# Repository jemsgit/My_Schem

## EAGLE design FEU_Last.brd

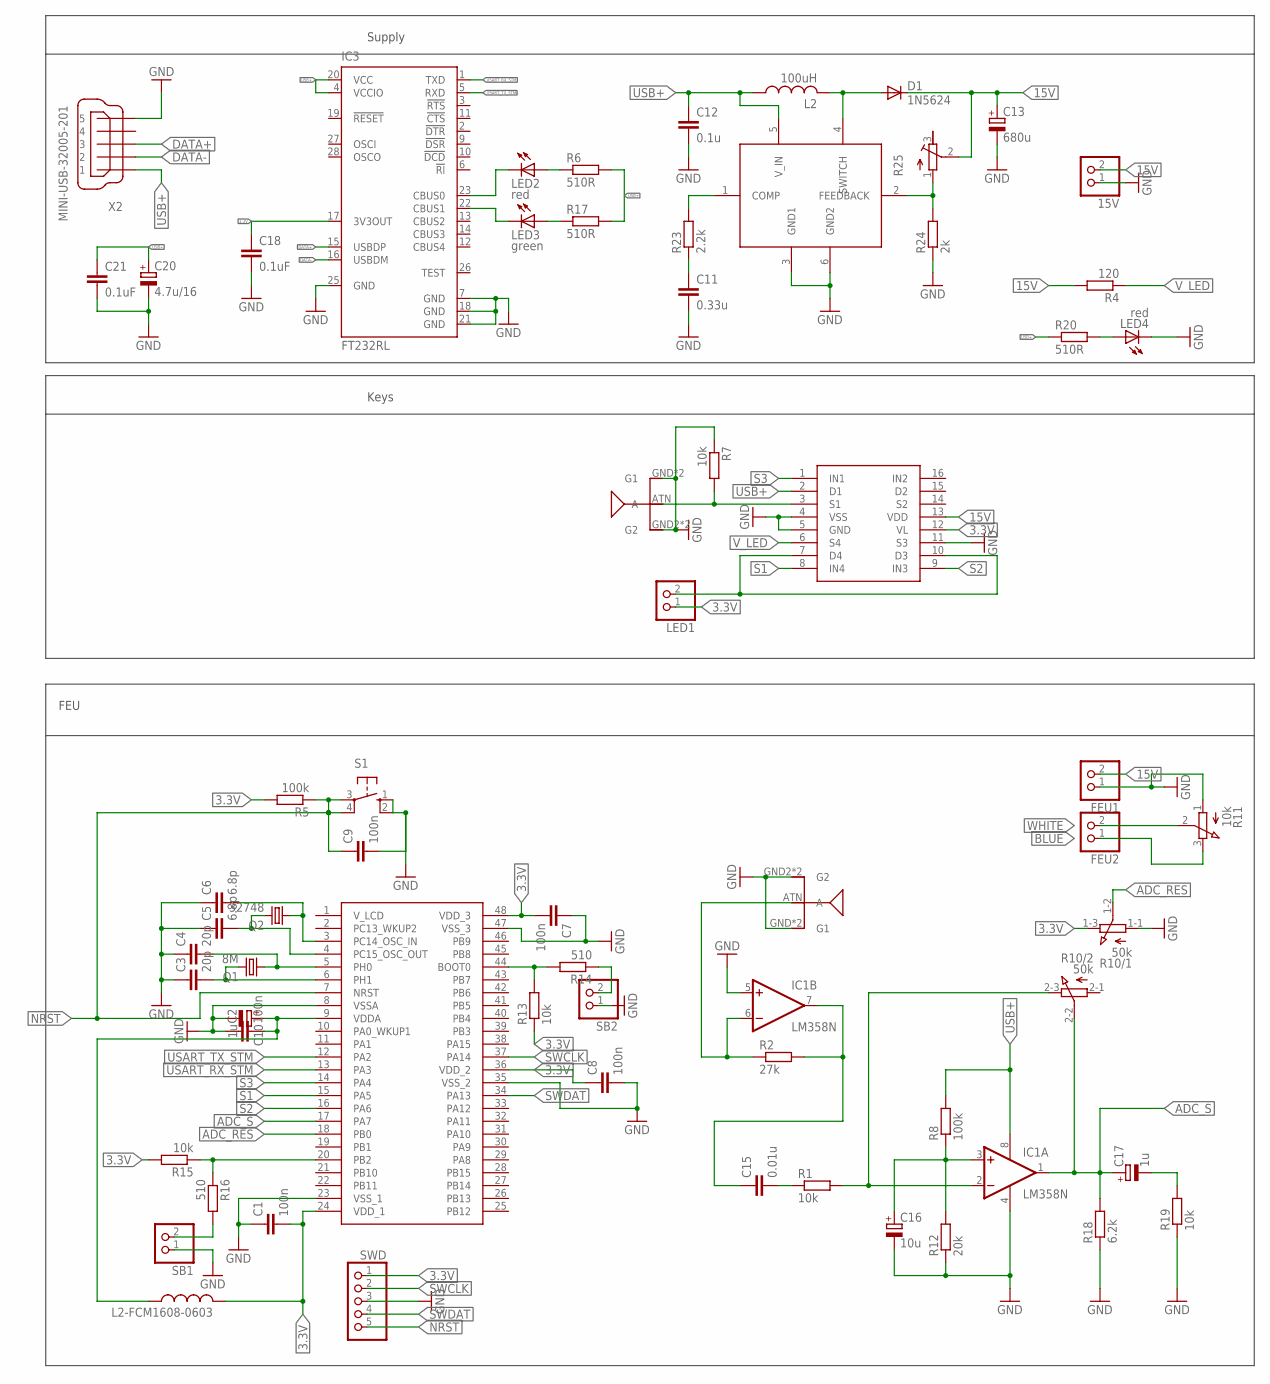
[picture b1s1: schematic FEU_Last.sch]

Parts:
15V: PINHD-1X2; 1X02
C1, C2, C7, C8, C9: 100n; C0805
C3, C4: 20p; C0805
C5, C6: 6.8p; C0805
C10: 1u; A/3216-18W
C11: 0.33u; C0805
C12: 0.1u; C0805
C13: 680u; E5-5
C15: 0.01u; C0805
C16: 10u; E3,5-8
C17: 1u; E3,5-8
C18, C21: 0.1uF; C0805
C20: 4.7u/16; E2-5
D1: 1N5624; DO201-15
FEU1, FEU2: PINHD-1X2; 1X02
IC1: LM358N; DIL08
IC3: FT232RL; SSOP28
L2: 100uH; 0207/5V
L2-FCM1608-0603: L-USL3216C; L3216C
LED1: PINHD-1X2; 1X02
LED2, LED4: red; CHIPLED_1206
LED3: green; CHIPLED_1206
Q1: 8M; HC49/S
Q2: 32748; TC26H
R1, R7, R13, R19: 10k; R0805
R2: 27k; R0805
R4: 120; R0805
R5, R8: 100k; R0805
R6, R17, R20: 510R; R0805W
R10: 50k; 3RP/1610G
R11: 10k; 3RP/1610N
R12: 20k; R0805
R14, R16: 510; R0805
R15: 10k; M0805
R18: 6.2k; R0805
R23: 2.2k; R0805
R24: 2k; R0805
R25: R-TRIMM3339P; RTRIM3339P
S1: 10-XX; B3F-10XX
SB1, SB2: PINHD-1X2; 1X02
SWD: PINHD-1X5; 1X05
U$1: STM32L152C6; LQFP48
U$2, U$3: GSM_ANT; GSM
U$4: LM2577; TO263-5
U$5: ADG433BN; DIL16
X2: MINI-USB-32005-201; 32005-201

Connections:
3.3V: C1.2, C7.2, C8.1, C18.1, IC3.17 (3V3OUT), L2-FCM1608-0603.2, LED1.1, R5.2, R10.1-3 (E), R13.1, R15.2, SWD.1, U$1.24 (VDD_1), U$1.36 (VDD_2), U$1.48 (VDD_3), U$5.12 (VL)
15V: 15V.2, C13.+, D1.C, FEU1.2, R4.2, R25.2 (S), U$5.13 (VDD)
ADC_RES: R10.1-2 (S), U$1.18 (PB0)
ADC_S: C17.+, IC1.1 (OUT), R10.2-2 (S), R18.2, U$1.17 (PA7)
BLUE: FEU2.1, R11.3 (E)
DATA+: IC3.15 (USBDP), X2.3
DATA-: IC3.16 (USBDM), X2.2
GND: 15V.1, C1.1, C2.1, C3.1, C4.1, C5.1, C6.1, C7.1, C8.2, C9.2, C10.-, C11.2, C12.2, C13.-, C16.-, C18.2, C20.-, C21.2, FEU1.1, IC1.4 (V-), IC1.5 (+IN), IC3.7 (GND), IC3.18 (GND), IC3.21 (GND), IC3.25 (GND), LED4.C, R7.1, R10.1-1 (A), R11.1 (A), R12.1, R18.1, R19.1, R24.1, S1.1 (S), S1.2 (S1), SB1.1, SB2.1, SWD.3, U$1.8 (VSSA), U$1.23 (VSS_1), U$1.35 (VSS_2), U$1.47 (VSS_3), U$2.GND (G1), U$2.GND1 (G1), U$2.GND2 (G2), U$2.GND3 (G2), U$3.GND (G1), U$3.GND1 (G1), U$3.GND2 (G2), U$3.GND3 (G2), U$4.3 (GND1), U$4.6 (GND2), U$5.4 (VSS), U$5.5 (GND), U$5.11 (S3), X2.5
unnamed: C4.2, Q1.1, U$1.5 (PH0)
unnamed: C3.2, Q1.2, U$1.6 (PH1)
unnamed: IC3.22 (CBUS1), LED3.C
unnamed: LED1.2, U$5.7 (D4), U$5.10 (D3)
unnamed: IC3.23 (CBUS0), LED2.C
unnamed: IC1.6 (-IN), R2.1, U$2.ATN (A)
unnamed: C15.1, IC1.7 (OUT), R2.2
unnamed: C15.2, R1.1
unnamed: C16.+, IC1.3 (+IN), R8.1, R12.2
unnamed: IC1.2 (-IN), R1.2, R10.2-3 (E)
unnamed: LED2.A, R6.1
unnamed: C5.2, Q2.2, U$1.4 (PC15_OSC_OUT)
unnamed: C6.2, Q2.1, U$1.3 (PC14_OSC_IN)
unnamed: C2.2, C10.+, L2-FCM1608-0603.1, U$1.9 (VDDA)
unnamed: R13.2, R14.2, U$1.44 (BOOT0)
unnamed: R16.2, SB1.2
unnamed: R14.1, SB2.2
unnamed: R15.1, R16.1, U$1.20 (PB2)
unnamed: C17.-, R19.2
unnamed: LED3.A, R17.1
unnamed: R7.2, U$3.ATN (A), U$5.3 (S1)
unnamed: LED4.A, R20.2
unnamed: R23.2, U$4.1 (COMP)
unnamed: C11.1, R23.1
unnamed: R24.2, R25.1 (E), U$4.2 (FEEDBACK)
unnamed: D1.A, L2.2, U$4.4 (SWITCH)
NRST: C9.1, R5.1, S1.3, S1.4 (P1), SWD.5, U$1.7 (NRST)
S1: U$1.15 (PA5), U$5.8 (IN4)
S2: U$1.16 (PA6), U$5.9 (IN3)
S3: U$1.14 (PA4), U$5.1 (IN1)
SWCLK: SWD.2, U$1.37 (PA14)
SWDAT: SWD.4, U$1.34 (PA13)
USART_RX_STM: IC3.1 (TXD), U$1.13 (PA3)
USART_TX_STM: IC3.5 (RXD), U$1.12 (PA2)
USB+: C12.1, C20.+, C21.1, IC1.8 (V+), IC3.4 (VCCIO), IC3.20 (VCC), L2.1, R6.2, R8.2, R17.2, R20.1, U$4.5 (V_IN), U$5.2 (D1), X2.1
V_LED: R4.1, U$5.6 (S4)
WHITE: FEU2.2, R11.2 (S)

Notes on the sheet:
Supply
Keys
FEU

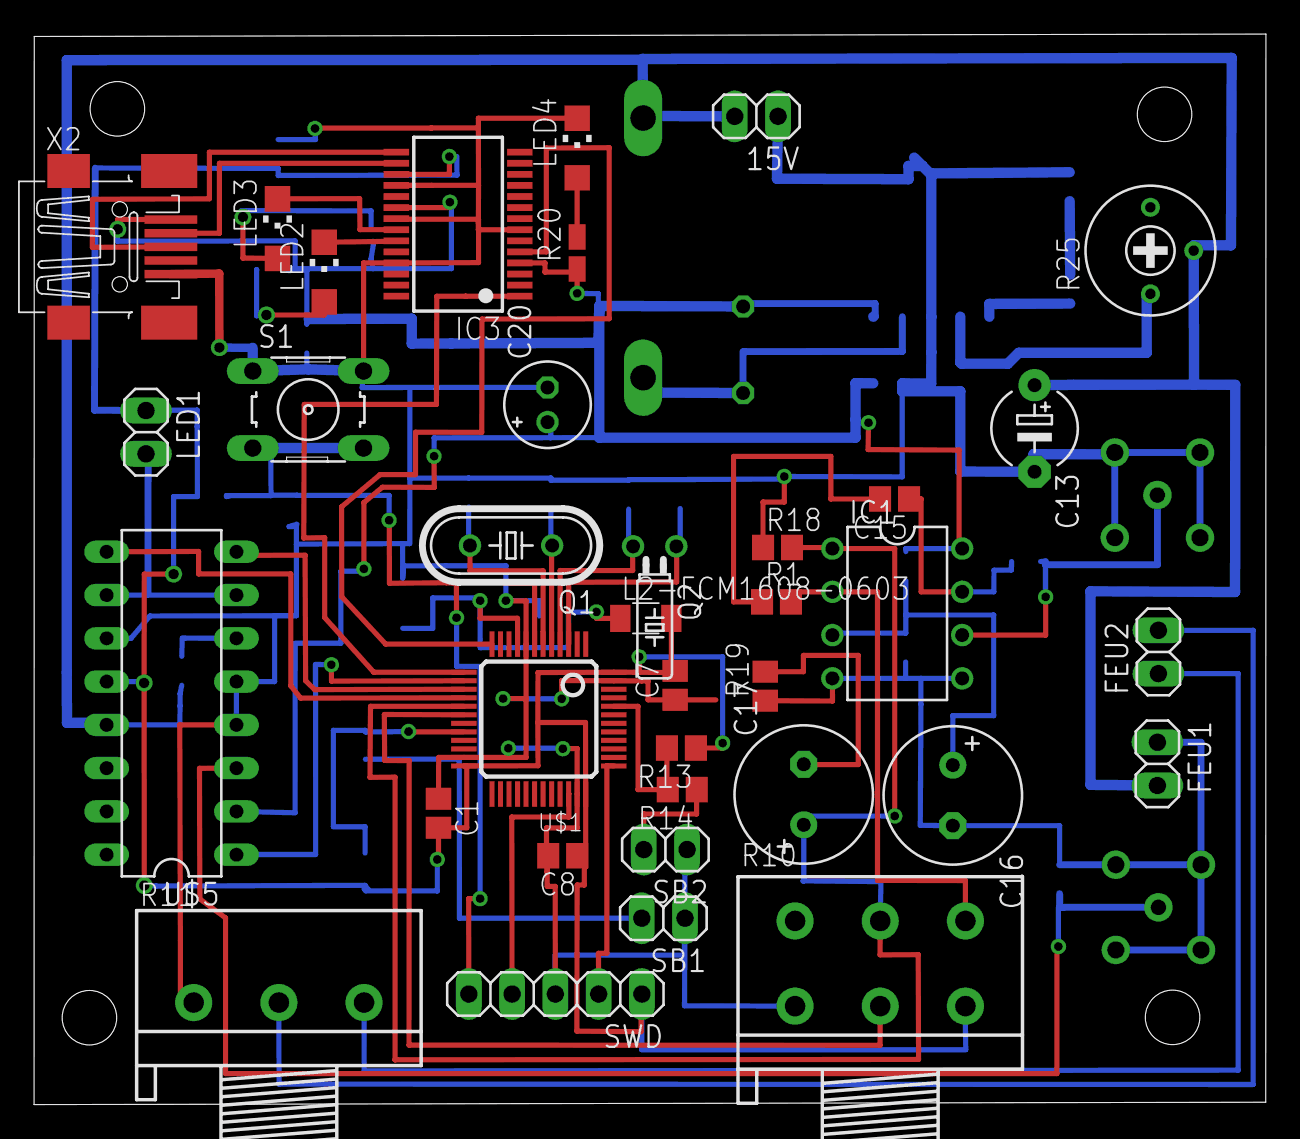
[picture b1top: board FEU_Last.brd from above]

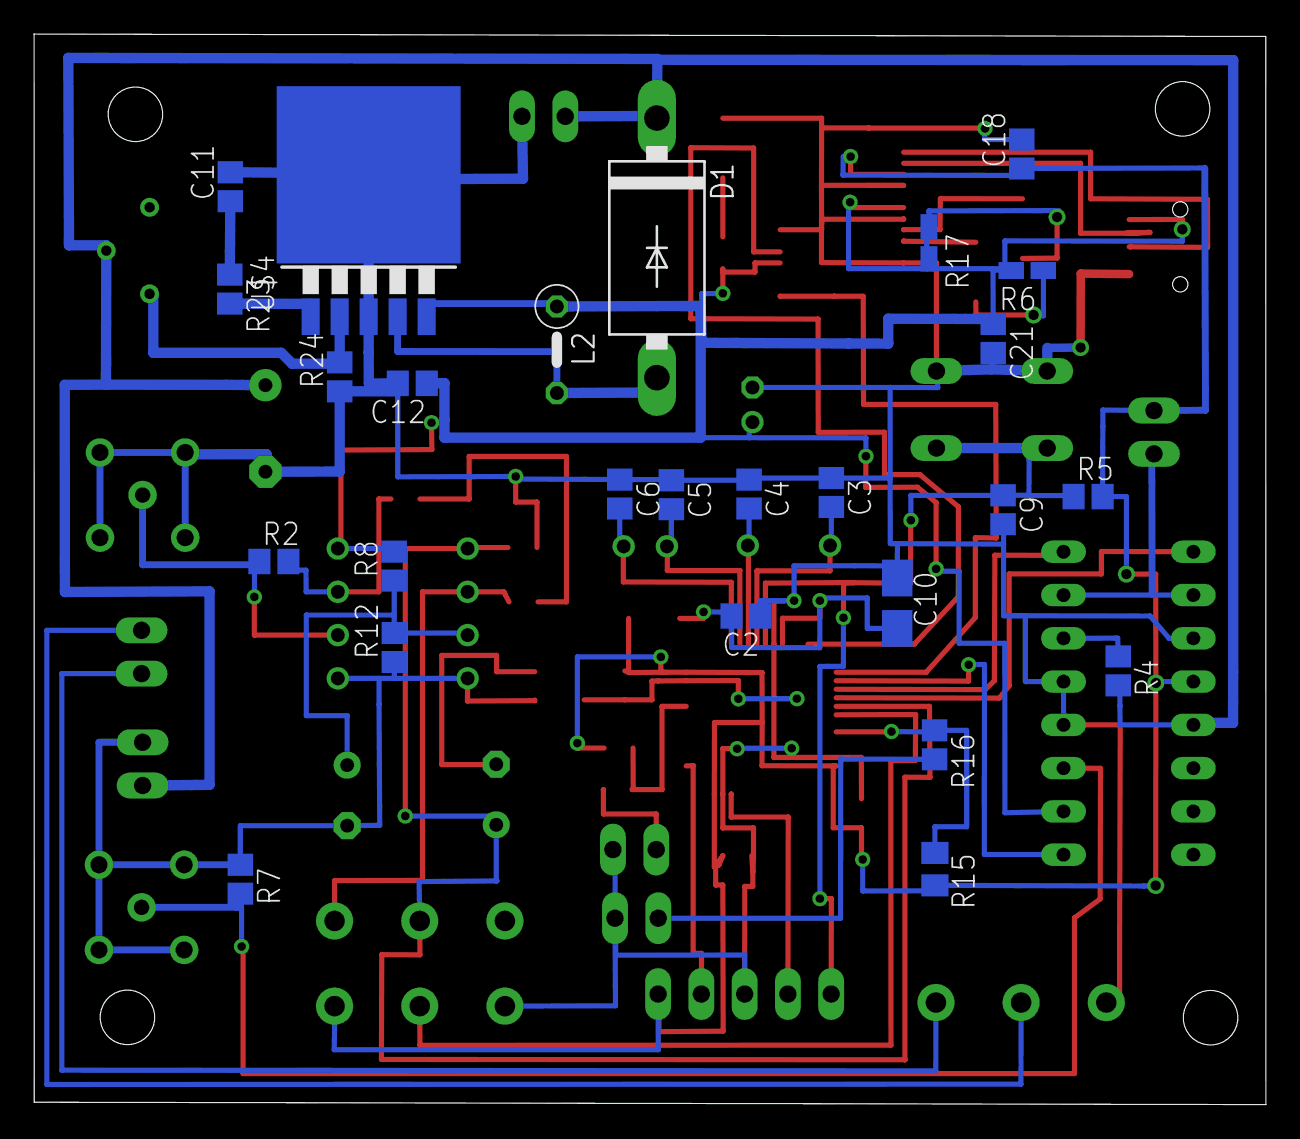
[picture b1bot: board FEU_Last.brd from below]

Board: 2 copper layers, 72.3 x 62.8 mm, 64 parts (26 on the bottom side), 45 nets.

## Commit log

2014-06-23 Schematic for STM32 Hamamatsu control
2014-06-24 Add BRD
2014-06-24 BRD 1
2014-06-25 BRD 2
2014-06-25 BRD 3
2014-06-26 BRD 4
2014-06-26 BRD 5
2014-06-26 BRD 6
2014-06-26 BRD 7
2014-06-27 BRD 8
2014-07-07 New version
2014-07-09 New BRD 2
2014-07-09 Schematic and board for factory v.1
2014-07-10 Factory board with FT232
2014-07-10 Factory board with FT232- 2
2014-07-11 Factory board with FT232- 3
2014-08-25 Add current-to voltage converter
